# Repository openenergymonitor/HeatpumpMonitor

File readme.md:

# Heatpump Monitor

This is a technical github repository for OpenEnergyMonitor open hardware and software heat-pump performance monitoring development.

## Rationale

Heat-pumps are a key component of zero carbon energy systems making it possible to provide heating efficiently from renewable energy, they are featured in many zero carbon energy scenarios such as ZeroCarbonBritain developed by the Centre for Alternative Technology and are also highlighted in David MacKay's book Sustainable Energy without the hot air.

By monitoring a heat-pump its possible to see how well it is working, diagnose problems and get a better understanding of how a key potentially zero carbon heating solution works, data gathered and shared from well performing systems could help de-mystify heat-pump operation and help improve performance by diagnosing any problems early.

## Getting started

The heat pump monitoring application guide in the main OpenEnergyMonitor guide is a good place to start, covering the different options, including the use of the main OpenEnergyMonitor hardware:

[https://guide.openenergymonitor.org/applications/heatpump](https://guide.openenergymonitor.org/applications/heatpump)

## Hardware

### EmonPi or EmonTx based heat pump monitor

<table>
<tr><td>

</td><td>
<b>Electricity consumption and system temperatures</b><br>
<p>Monitor electricity consumption and system temperatures using clip-on CT sensors and one-wire temperature sensors connected to an emonPi or emonTx. This provides the simplest solution for installation on existing systems. See <a href="https://guide.openenergymonitor.org/applications/heatpump">main guide for details</a>.</p>
</td>
</tr>
<tr><td>

</td><td>
<b>Using external MBUS reader module</b><br>
<p>An external MBUS reader connected to the emonPi or emonBase can be used to read from high accuracy electricity and heat meters. See <a href="https://guide.openenergymonitor.org/applications/heatpump">main guide for details</a>.</p>
</td>
</tr>
</table>

### [New: RaspberryPi & MBUS based heat pump monitor](HeatpumpMonitorPi)

<table>
<tr><td>

</td><td>
<p>This is a new heat pump monitor board designed specifically for interfacing with MID standard electricity and heat meters via MBUS. It has a RaspberryPi at it’s core running our emonSD image enabling local or/and remote logging and data visualisation.</p>
</td>
</tr>
</table>

### [Original through-hole heat pump monitor](HeatpumpMonitorTH)

<table>
<tr><td>

</td><td>
<b>Main Features:</b><br>
<ul>
<li>CT current and ACAC voltage based electricity monitoring</li>
<li>Pulse counting or IRDA Elster meter reader</li>
<li>Analog inputs for Vortex Flow Sensor (VFS) option (e.g Sika, Grundfos)</li>
<li>MBUS reader for kamstrup heat meters (402, 403)</li>
<li>4x individually broken out DS18B20 temperature sensor connections</li>
<li>Arduino ATmega328 core</li>
<li>Connectivity options: ESP-12 WIFI, RaspberryPI header, RFM69</li>
</ul>
</td>
</tr>
</table>

### Mini Boards

**USB to MBUS**

- [USB to MBUS v1 SMT](https://github.com/openenergymonitor/HeatpumpMonitor/tree/master/USB_MBUS_Reader)

**WiFi MBUS Reader**

- [WiFi MBUS Reader v1 (Through-hole)](https://github.com/openenergymonitor/HeatpumpMonitor/tree/master/Hardware/WiFi_MBUS_Reader/v1_TH)
- [WiFi MBUS Reader v1 SMT](https://github.com/openenergymonitor/HeatpumpMonitor/tree/master/Hardware/WiFi_MBUS_Reader/v1)

## Heat pump monitoring dashboard

Emoncms includes an application specific heat pump dashboard available in the Apps module. The following video gives a good overview of what this dashboard can do, how to access daily electricity consumption and heat output data as well as detailed system temperature and power data.

There's also a little feature shown briefly at the end that simulates the heat output and COP of the heat pump based on the Carnot COP equation.

[YouTube: Introduction to the Emoncms heat pump dashboard](https://www.youtube.com/watch?v=jBY1Sx3LR2o)

It's also worth checking out David Bowen (@MyForest on the forum's) heat pump app, see forum post: [Heat Pump Experimentation App - Release News](https://community.openenergymonitor.org/t/heat-pump-experimentation-app-release-news/13423).

The My Heatpump app includes a feature to simulate the COP and heat output of a heat pump from the flow temperature, outside temperature and electrical power input. The equations used are documented here: https://github.com/emoncms/dynamic/blob/master/docs/heatpumpmodel.md

## Blogs and further reading

- **Blog post:** [Heatpumps in the ZeroCarbonBritain model by the Centre for Alternative Technology.](https://blog.openenergymonitor.org/2015/12/heatpumps-in-zerocarbonbritain-model-by)
- **Blog post:** [Heat pump Testing: Initial results](https://blog.openenergymonitor.org/2016/02/heat-pump-testing-initial-results)
- **[John Cantor's heat pump monitoring blog](https://heatpumps.co.uk/technical/energy-monitoring)**

## Licence

This project is open source software and hardware.

The Arduino firmware is available under the GPL v3 Licence. 

The Web Dashboard is available under the GNU Affero General Public License and is based on emoncms.

The hardware design (schematics, board files and gerber) files are licensed under the [Creative Commons Attribution-ShareAlike 3.0 Unported License](http://creativecommons.org/licenses/by-sa/3.0/) and follow the terms of the [OSHW (Open-source hardware) Statement of Principles 1.0.](http://freedomdefined.org/OSHW)

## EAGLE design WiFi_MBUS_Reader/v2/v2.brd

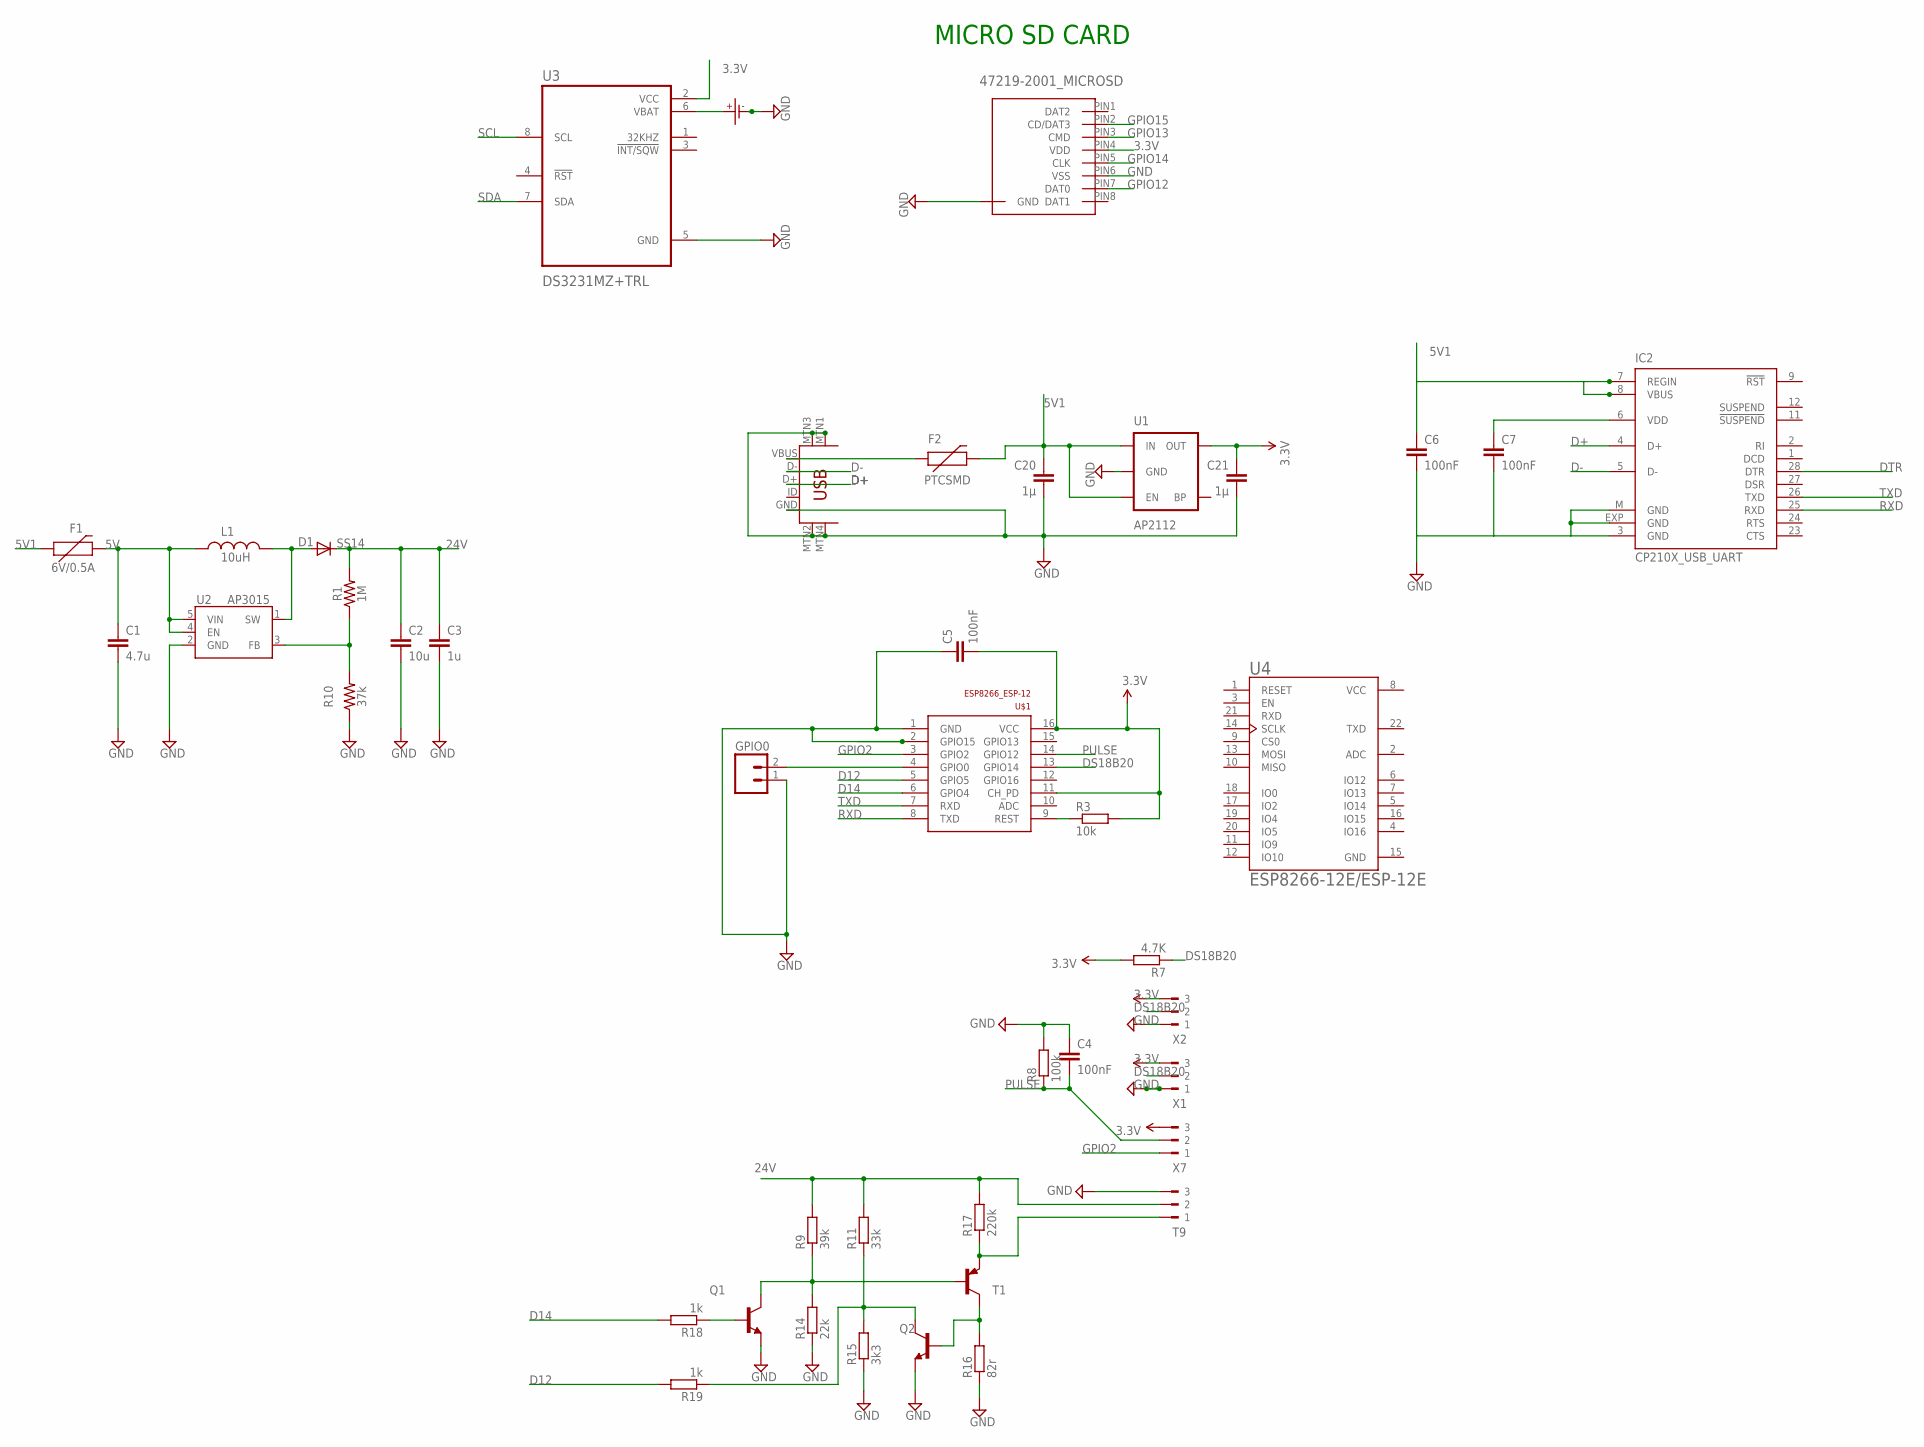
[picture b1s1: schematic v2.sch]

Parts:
C1: 4.7u; 0805
C2: 10u; 1206
C3: 1u; 1206
C4, C5: 100nF; C0603
C6, C7: 100nF; 0603-CAP
C20, C21: 1µ; C0603
CR1: CR1220SMD; MPN Harwin S8411-45R
D1: SS14; SOD-123
F1: 6V/0.5A; 1206
F2: PTCSMD; PTC-1206
GPIO0: M02PTH; 1X02
IC2: CP210X_USB_UART; MLP28
L1: 10uH; CR54
MICRO_SD: 47219-2001_MICROSD
Q1, Q2: BC808-NPN-SOT23-BEC; SOT23-BEC
R1: 1M; 0805
R3: 10k; R0603
R7: 4.7K; R0603
R8: 100k; R0603
R9: 39k; R0603
R10: 37k; 0805
R11: 33k; R0603
R14: 22k; R0603
R15: 3k3; R0603
R16: 82r; R0603
R17: 220k; R0603
R18, R19: 1k; R0603
T1: BC807-16-PNP-SOT23-BEC; SOT23-BEC
T9: 180-3
U1: AP2112; SOT23-5
U2: AP3015; SOT-23-5
U3: DS3231MZ+TRL; SOIC127P600X175-8N
U4: ESP8266-12E/ESP-12E; XCVR_ESP8266-12E/ESP-12E
U$1: ESP8266_ESP-12; ESP8266-ESP12
U$10: USB-MINIB-5PIN; USB-MINIB-CISECO
X1, X2, X7: 180-3

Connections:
3.3V: C5.2, C21.1, MICRO_SD.PIN4 (VDD), R3.2, R7.2, U1.5 (OUT), U3.2 (VCC), U$1.11 (CH_PD), U$1.16 (VCC), X1.3, X2.3, X7.3
5V: C1.1, F1.2, L1.P$1 (1), U2.4 (EN), U2.5 (VIN)
5V1: C6.1, C20.1, F1.1, F2.2, IC2.7 (REGIN), IC2.8 (VBUS), U1.1 (IN), U1.3 (EN)
24V: C2.1, C3.1, D1.C, R1.2, R9.2, R11.2, R17.2, T9.2
D12: R19.2, U$1.5 (GPIO5)
D14: R18.2, U$1.6 (GPIO4)
D+: IC2.4 (D+), U$10.D+
D-: IC2.5 (D-), U$10.D-
DS18B20: R7.1, U$1.13 (GPIO14), X1.2, X2.2
DTR: IC2.28 (DTR)
GND: C1.2, C2.2, C3.2, C4.1, C5.1, C6.2, C7.2, C20.2, C21.2, CR1.P- (P$-), GPIO0.1, IC2.3 (GND), IC2.EXP (GND), IC2.M (GND), MICRO_SD.P$1 (GND), MICRO_SD.P$2 (GND), MICRO_SD.P$3 (GND), MICRO_SD.P$4 (GND), MICRO_SD.PIN6 (VSS), Q1.E, Q2.E, R8.2, R10.1, R14.1, R15.1, R16.1, T9.3, U1.2 (GND), U2.2 (GND), U3.5 (GND), U4.15 (GND), U$1.1 (GND), U$1.2 (GPIO15), U$10.GND, U$10.MTN1 (MTN2), U$10.MTN2 (MTN3), U$10.MTN3 (MTN1), U$10.MTN4, X1.1, X2.1
GPIO2: U$1.3 (GPIO2), X7.1
GPIO12: MICRO_SD.PIN7 (DAT0)
GPIO13: MICRO_SD.PIN3 (CMD)
GPIO14: MICRO_SD.PIN5 (CLK)
GPIO15: MICRO_SD.PIN2 (CD/DAT3)
unnamed: C7.1, IC2.6 (VDD)
unnamed: F2.1, U$10.VBUS
unnamed: R1.1, R10.2, U2.3 (FB)
unnamed: D1.A, L1.P$2 (2), U2.1 (SW)
unnamed: CR1.P+ (P$+), U3.6 (VBAT)
unnamed: R17.1, T1.E, T9.1
unnamed: Q2.B, R16.2, T1.C
unnamed: Q1.C, R9.1, R14.2, T1.B
unnamed: Q2.C, R11.1, R15.2, R19.1
unnamed: Q1.B, R18.1
unnamed: GPIO0.2, U$1.4 (GPIO0)
unnamed: R3.1, U$1.9 (REST)
PULSE: C4.2, R8.1, U$1.14 (GPIO12), X7.2
RXD: IC2.25 (RXD), U$1.8 (TXD)
SCL: U3.8 (SCL)
SDA: U3.7 (SDA)
TXD: IC2.26 (TXD), U$1.7 (RXD)
VCC: U4.8 (VCC)

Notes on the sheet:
MICRO SD CARD

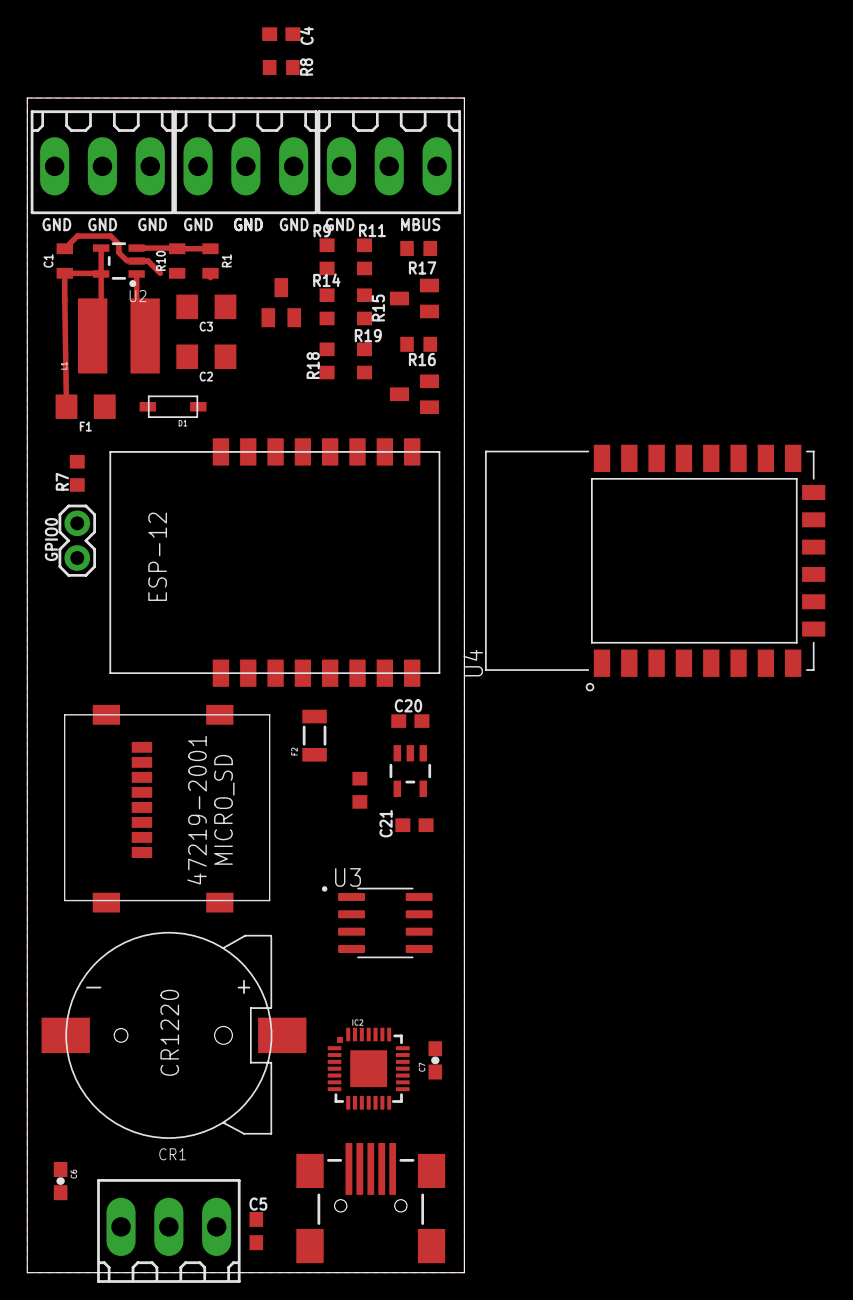
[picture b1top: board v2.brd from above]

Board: 2 copper layers, 32.0 x 86.0 mm, 44 parts (1 on the bottom side), 26 nets.

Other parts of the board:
LOGO1: OSHW_LOGO_6MILX0200-NT; OSHW_6X200_NOTEXT

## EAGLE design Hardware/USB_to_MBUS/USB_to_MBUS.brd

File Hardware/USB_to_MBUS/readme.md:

# USB to MBUS

A simple USB MBUS reader with on-board boost converter and CP2102 USB to UART chip. Designed for reading data from heat pump heat meters and interfacing directly with a RaspberryPi via a USB cable.

**Features**

- MBUS Reader circuit (original circuit by [Tomas Menzi](https://github.com/rscada/libmbus/tree/master/hardware))
- On-board boost converter (based on [Taaralabs](https://taaralabs.eu/m-bus-uart-converter/))
- CP2102 USB to UART chip

**Software**

The board can be used with the EmonHub MBUS Interfacer. This interfacer is designed to look for specific useful parameters for electric and heat metering (It does not implement the full MBUS spec). It will typically return flow and return temperatures, flow rate, heat output, and cumulative heat energy for heat meters that support these parameters.

https://guide.openenergymonitor.org/integrations/emonhub-interfacers/#mbus-reader-for-electric-and-heat-meters

## Schematic

[USB_to_MBUS.sch](USB_to_MBUS.sch)

## Board

[USB_to_MBUS.brd](USB_to_MBUS.brd)

The hardware design (schematics, board files and gerber) files are licensed under the [Creative Commons Attribution-ShareAlike 3.0 Unported License](http://creativecommons.org/licenses/by-sa/3.0/) and follow the terms of the [OSHW (Open-source hardware) Statement of Principles 1.0.](http://freedomdefined.org/OSHW)

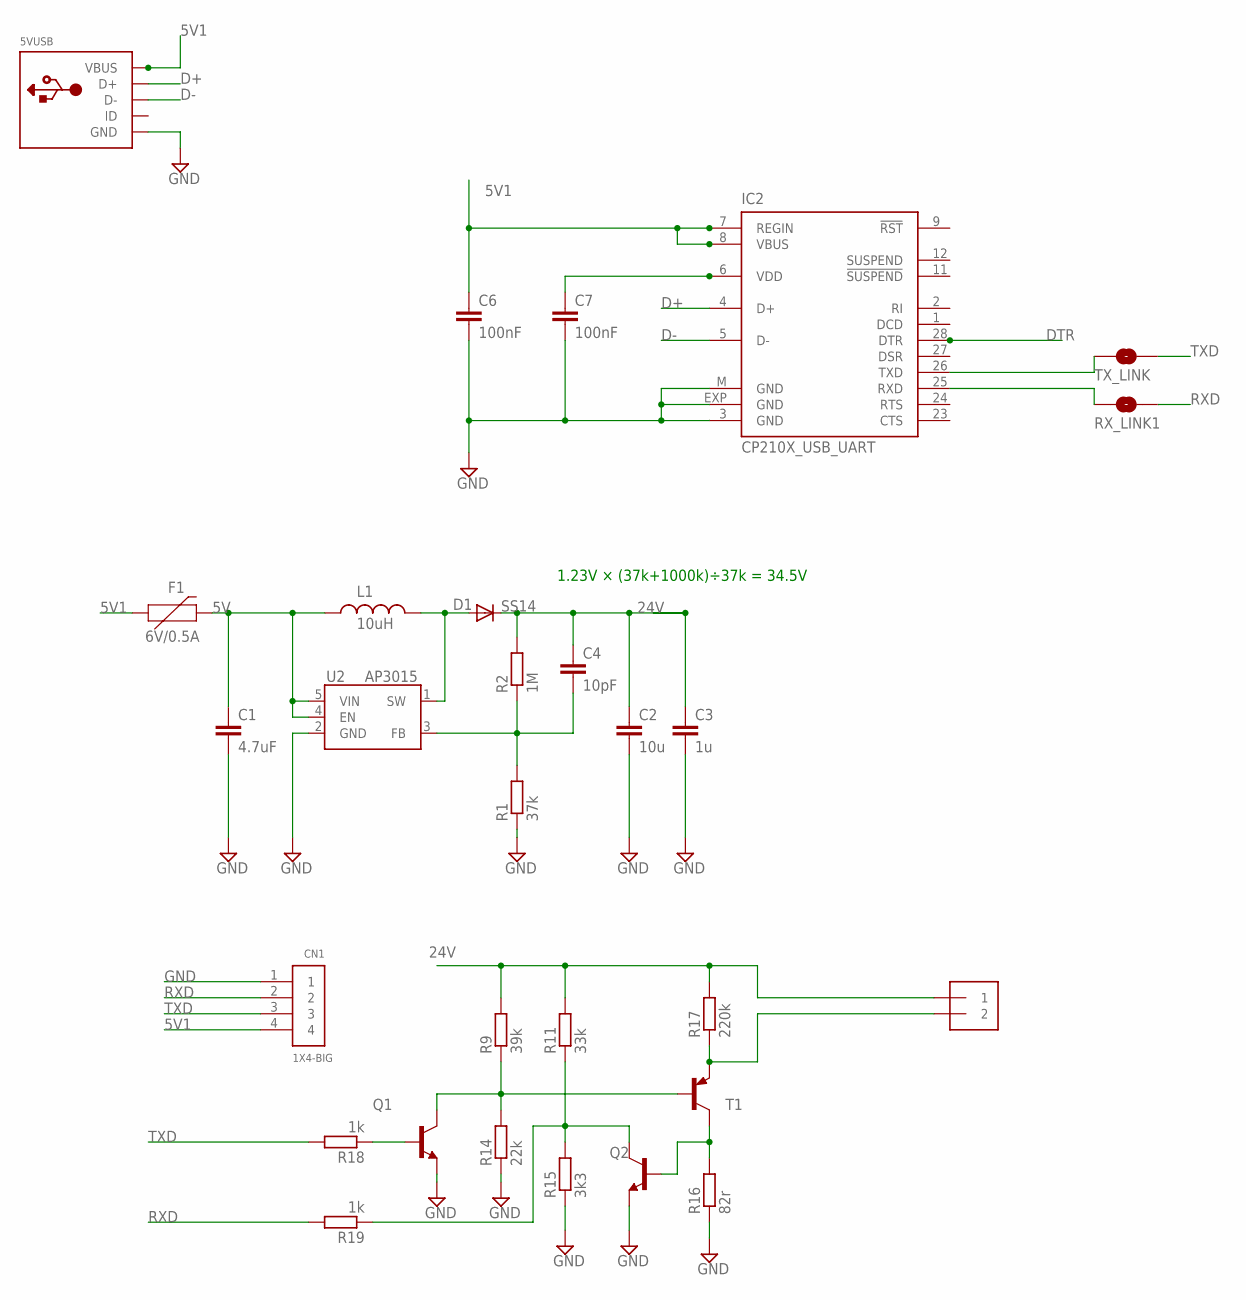
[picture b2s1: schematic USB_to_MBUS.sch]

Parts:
5VUSB: USBMOLEX; USB-MINIB-THM-MOLEX
C1: 4.7uF; 0603
C2: 10u; 1206
C3: 1u; 1206
C4: 10pF; 0603-CAP
C6, C7: 100nF; 0603-CAP
CN1: 1X4-BIG; 1X04-BIG
D1: SS14; SOD-123
F1: 6V/0.5A; 1206
IC2: CP210X_USB_UART; MLP28
J1: 1X2-3.5MM
L1: 10uH; CR54
Q1, Q2: BC808-NPN-SOT23-BEC; SOT23-BEC
R1: 37k; R0603
R2: 1M; R0603
R9: 39k; R0603
R11: 33k; R0603
R14: 22k; R0603
R15: 3k3; R0603
R16: 82r; R0603
R17: 220k; R0603
R18, R19: 1k; R0603
RX_LINK1: SOLDERJUMPERNC; SJ_2S
T1: BC807-16-PNP-SOT23-BEC; SOT23-BEC
TX_LINK: SOLDERJUMPERNC; SJ_2S
U2: AP3015; SOT-23-5

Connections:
5V: C1.1, F1.2, L1.P$1 (1), U2.4 (EN), U2.5 (VIN)
5V1: 5VUSB.VBUS, C6.1, CN1.4, F1.1, IC2.7 (REGIN), IC2.8 (VBUS)
24V: C2.1, C3.1, C4.1, D1.C, J1.1, R2.2, R9.2, R11.2, R17.2; also elsewhere on the board
D+: 5VUSB.D+, IC2.4 (D+)
D-: 5VUSB.D-, IC2.5 (D-)
DTR: IC2.28 (DTR)
GND: 5VUSB.GND, C1.2, C2.2, C3.2, C6.2, C7.2, CN1.1, IC2.3 (GND), IC2.EXP (GND), IC2.M (GND), Q1.E, Q2.E, R1.1, R14.1, R15.1, R16.1, U2.2 (GND)
unnamed: C7.1, IC2.6 (VDD)
unnamed: C4.2, R1.2, R2.1, U2.3 (FB)
unnamed: D1.A, L1.P$2 (2), U2.1 (SW)
unnamed: IC2.26 (TXD), TX_LINK.1
unnamed: IC2.25 (RXD), RX_LINK1.1
unnamed 12: J1.2, R17.1, T1.E; also elsewhere on the board
unnamed: Q2.B, R16.2, T1.C
unnamed: Q1.C, R9.1, R14.2, T1.B
unnamed: Q2.C, R11.1, R15.2, R19.1
unnamed: Q1.B, R18.1
RXD: CN1.2, R19.2, RX_LINK1.2
TXD: CN1.3, R18.2, TX_LINK.2

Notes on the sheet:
1.23V × (37k+1000k)÷37k = 34.5V

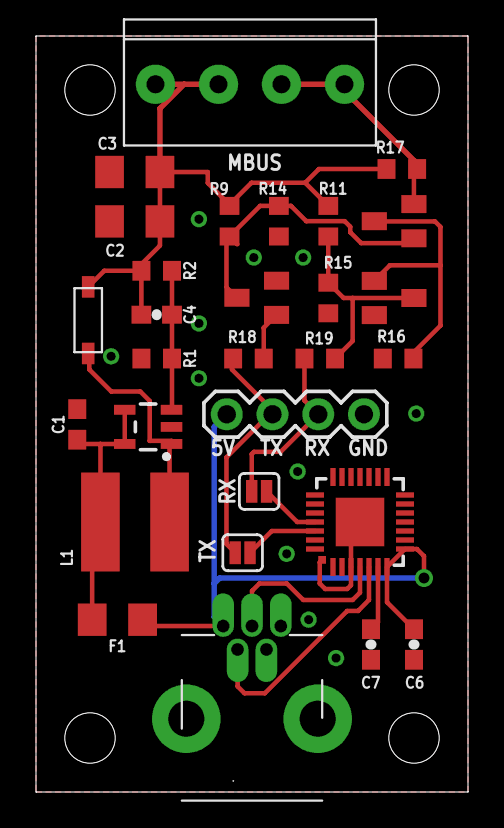
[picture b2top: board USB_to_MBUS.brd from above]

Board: 2 copper layers, 24.0 x 42.0 mm, 30 parts (1 on the bottom side), 18 nets.

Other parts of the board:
CN2: 1X4-3.5MM; 1X04-3.5MM
LOGO1: OSHW_LOGO_6MILX0200-NT; OSHW_6X200_NOTEXT

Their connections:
24V: CN2.3, CN2.4; also elsewhere on the board
unnamed 12: CN2.1, CN2.2; also elsewhere on the board

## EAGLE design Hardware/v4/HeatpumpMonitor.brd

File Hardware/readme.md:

# Heatpump monitor

This is a new design for a dedicated open source heatpump monitoring board with support for the reading of a kamstrup heatmeter or/and grundfos vortex flow sensor on board in addition to DS18B20 based temperature sensing and standard OpenEnergyMonitor electrictiy monitoring with CT current + ACAC voltage sensing.

In addition this board supports the esp-12 wifi module, raspberrypi gpio and a emonglcd display as optional extras.

This board is currently going through initial testing, if your interested in this unit and heatpump monitoring please get in contact: trystan.lea@openenergymonitor.org

## Schematic

[HeatpumpMonitor.brd](HeatpumpMonitor.brd)

## Board

[HeatpumpMonitor.sch](HeatpumpMonitor.sch)

The hardware design (schematics, board files and gerber) files are licensed under the [Creative Commons Attribution-ShareAlike 3.0 Unported License](http://creativecommons.org/licenses/by-sa/3.0/) and follow the terms of the [OSHW (Open-source hardware) Statement of Principles 1.0.](http://freedomdefined.org/OSHW)

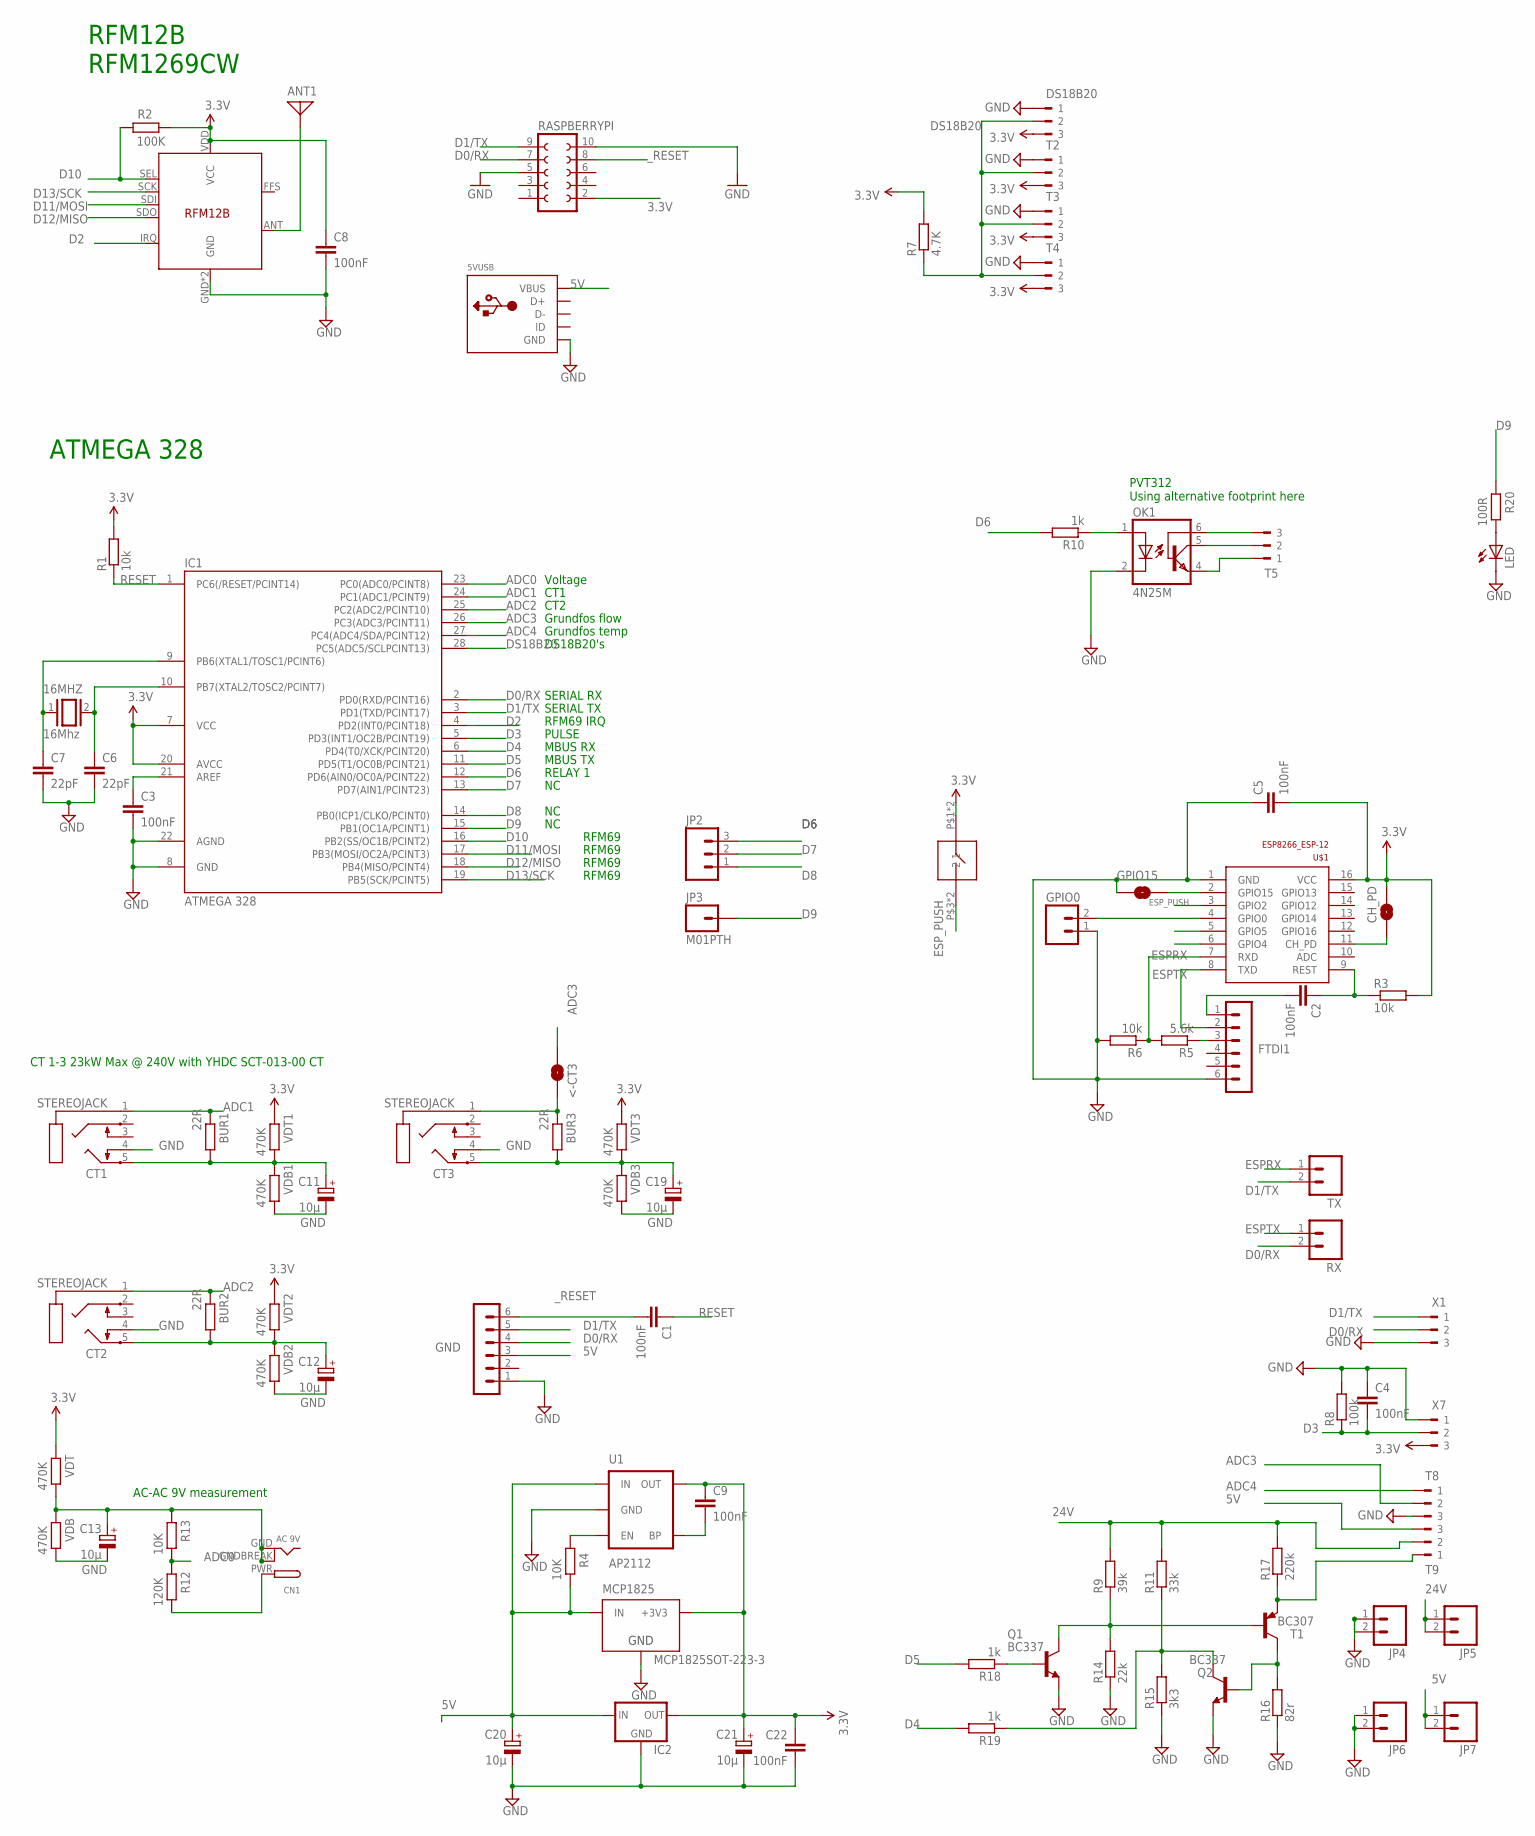
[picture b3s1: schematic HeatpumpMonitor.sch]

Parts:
5VUSB: USBMOLEX; USB-MINIB-THM-MOLEX
16MHZ: 16Mhz; QS
<-CT3: SOLDERJUMPERNO; SJ_2S-NO
ANT1: ANTENNA; PAD-01
BUR1, BUR2, BUR3: 22R; 0204/7
C1, C2, C3, C4, C5, C8, C22: 100nF; C025-024X044
C6, C7: 22pF; C2.5-2
C9: 100nF; C0603
C11, C12, C13, C19, C20, C21: 10µ; E1,8-4
CH_PD: SOLDERJUMPERNO; SJ_2S-NO
CN1: AC 9V; DCJACK_2MM_PTH
CT1, CT2, CT3: STEREOJACK; STX3100
DS18B20: 180-3
FTDI1: FTDI; MA06-1
GND: FTDI; MA06-1
GPIO0: M02PTH; 1X02
GPIO15: SOLDERJUMPERNO; SJ_2S-NO
IC1: ATMEGA 328; DIL28-3
IC2: 78XXS
JP2: M03PTH; 1X03
JP3: M01PTH; 1X01
JP4, JP5, JP6, JP7: M02PTH; 1X02
LED: LED3MM
MCP1825: MCP1825SOT-223-3; SOT-223
OK1: 4N25M; DIL06
Q1, Q2: BC337; TO92
R1, R3, R6: 10k; 0204/7
R2: 100K; 0204/7
R4: 10K; R0603
R5: 5.6k; 0204/7
R7: 4.7K; 0204/7
R8: 100k; 0207/2V
R9: 39k; 0204/7
R10, R18, R19: 1k; 0204/7
R11: 33k; 0204/7
R12: 120K; 0204/7
R13: 10K; 0204/7
R14: 22k; 0204/7
R15: 3k3; 0204/7
R16: 82r; 0204/7
R17: 220k; 0204/7
R20: 100R; 0204/7
RASPBERRYPI: FE05-2
RX: M02PTH; 1X02
T1: BC307; TO92
T2, T3, T4, T5, T8, T9: 180-3
TX: M02PTH; 1X02
U1: AP2112; SOT23-5
U$1: ESP8266_ESP-12; ESP8266-ESP12
U$2: KSEK43G"; KSEK43G
U$14: RFM12B
VDB, VDB1, VDB2, VDB3: 470K; 0204/7
VDT, VDT1, VDT2, VDT3: 470K; 0204/7
X1, X7: 180-3

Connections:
3.3V: C5.2, C8.1, C9.1, C21.+, C22.1, CH_PD.1, DS18B20.3, IC1.7 (VCC), IC1.20 (AVCC), IC2.OUT, MCP1825.3 (+3V3), R1.2, R2.1, R3.2, R7.2, RASPBERRYPI.2, T2.3, T3.3, T4.3, U1.5 (OUT), U$1.16 (VCC), U$2.P$1 (1), U$2.P$2 (1), U$14.VDD (VCC), VDT.2, VDT1.2, VDT2.2, VDT3.2, X7.3
5V: 5VUSB.VBUS, C20.+, GND.3, IC2.IN, JP7.1, JP7.2, MCP1825.1 (IN), R4.1, T9.3, U1.1 (IN)
24V: JP5.1, JP5.2, R9.2, R11.2, R17.2, T9.2
AC: CN1.PWR, R12.1
ADC0: IC1.23 (PC0(ADC0/PCINT8)), R12.2, R13.1
ADC1: BUR1.2, CT1.1, IC1.24 (PC1(ADC1/PCINT9))
ADC2: BUR2.2, CT2.1, IC1.25 (PC2(ADC2/PCINT10))
ADC3: <-CT3.2, IC1.26 (PC3(ADC3/PCINT11)), T8.2
ADC4: IC1.27 (PC4(ADC4/SDA/PCINT12)), T8.1
D0/RX: GND.4, IC1.2 (PD0(RXD/PCINT16)), RASPBERRYPI.7, RX.2, X1.2
D1/TX: GND.5, IC1.3 (PD1(TXD/PCINT17)), RASPBERRYPI.9, TX.2, X1.1
D2: IC1.4 (PD2(INT0/PCINT18)), U$14.IRQ
D3: C4.2, IC1.5 (PD3(INT1/OC2B/PCINT19)), R8.1, X7.2
D4: IC1.6 (PD4(T0/XCK/PCINT20)), R19.2
D5: IC1.11 (PD5(T1/OC0B/PCINT21)), R18.2
D6: IC1.12 (PD6(AIN0/OC0A/PCINT22)), JP2.3, R10.2
D7: IC1.13 (PD7(AIN1/PCINT23)), JP2.2
D8: IC1.14 (PB0(ICP1/CLKO/PCINT0)), JP2.1
D9: IC1.15 (PB1(OC1A/PCINT1)), JP3.1, R20.2
D10: IC1.16 (PB2(SS/OC1B/PCINT2)), R2.2, U$14.SEL
D11/MOSI: IC1.17 (PB3(MOSI/OC2A/PCINT3)), U$14.SDI
D12/MISO: IC1.18 (PB4(MISO/PCINT4)), U$14.SDO
D13/SCK: IC1.19 (PB5(SCK/PCINT5)), U$14.SCK
DIG1: ANT1.1, U$14.ANT
DS18B20: DS18B20.2, IC1.28 (PC5(ADC5/SCLPCINT13)), R7.1, T2.2, T3.2, T4.2
ESPRX: R5.2, R6.1, TX.1, U$1.7 (RXD)
ESPTX: FTDI1.2, RX.1, U$1.8 (TXD)
ESP_PUSH: U$1.3 (GPIO2), U$2.P$3 (2), U$2.P$4 (2)
GND: 5VUSB.GND, C3.2, C4.1, C5.1, C6.2, C7.2, C8.2, C11.-, C12.-, C13.-, C19.-, C20.-, C21.-, C22.2, CT1.4, CT2.4, CT3.4, DS18B20.1, FTDI1.6, GND.1, GPIO0.1, GPIO15.2, IC1.8 (GND), IC1.22 (AGND), IC2.GND, JP4.1, JP4.2, JP6.1, JP6.2, LED.K (C), MCP1825.2 (GND), OK1.2 (C), Q1.1 (E), Q2.1 (E), R6.2, R8.2, R14.1, R15.1, R16.1, RASPBERRYPI.5, RASPBERRYPI.10, T2.1, T3.1, T4.1, T8.3, U1.2 (GND), U$1.1 (GND), U$14.GND, U$14.P$12 (GND), VDB.1, VDB1.1, VDB2.1, VDB3.1, X1.3, X7.1
unnamed: 16MHZ.2, C6.1, IC1.10 (PB7(XTAL2/TOSC2/PCINT7))
unnamed: BUR2.1, C12.+, CT2.5, VDB2.2, VDT2.1
unnamed: C2.2, FTDI1.1
unnamed: <-CT3.1, BUR3.2, CT3.1
unnamed: OK1.1 (A), R10.1
unnamed: OK1.6 (BAS), T5.3
unnamed: C9.2, U1.4 (BP)
unnamed: BUR3.1, C19.+, CT3.5, VDB3.2, VDT3.1
unnamed: OK1.5 (COL), T5.2
unnamed: OK1.4 (EMI), T5.1
unnamed: R4.2, U1.3 (EN)
unnamed: 16MHZ.1, C7.1, IC1.9 (PB6(XTAL1/TOSC1/PCINT6))
unnamed: R17.1, T1.1 (E), T9.1
unnamed: LED.A, R20.1
unnamed: Q2.2 (B), R16.2, T1.3 (C)
unnamed: Q1.3 (C), R9.1, R14.2, T1.2 (B)
unnamed: C3.1, IC1.21 (AREF)
unnamed: Q2.3 (C), R11.1, R15.2, R19.1
unnamed: Q1.2 (B), R18.1
unnamed: GPIO15.1, U$1.2 (GPIO15)
unnamed: GPIO0.2, U$1.4 (GPIO0)
unnamed: C13.+, CN1.GND, CN1.GNDBREAK, R13.2, VDB.2, VDT.1
unnamed: FTDI1.3, R5.1
unnamed: BUR1.1, C11.+, CT1.5, VDB1.2, VDT1.1
unnamed: CH_PD.2, U$1.11 (CH_PD)
unnamed: C2.1, R3.1, U$1.9 (REST)
RESET: C1.1, IC1.1 (PC6(/RESET/PCINT14)), R1.1
_RESET: C1.2, GND.6, RASPBERRYPI.8

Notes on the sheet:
ATMEGA 328
RFM12B RFM1269CW
CT 1-3 23kW Max @ 240V with YHDC SCT-013-00 CT
AC-AC 9V measurement
Voltage
CT1
CT2
SERIAL RX
SERIAL TX
RFM69 IRQ
MBUS RX
MBUS TX
PULSE
Grundfos flow
Grundfos temp
DS18B20's
RELAY 1
RFM69
PVT312 Using alternative footprint here

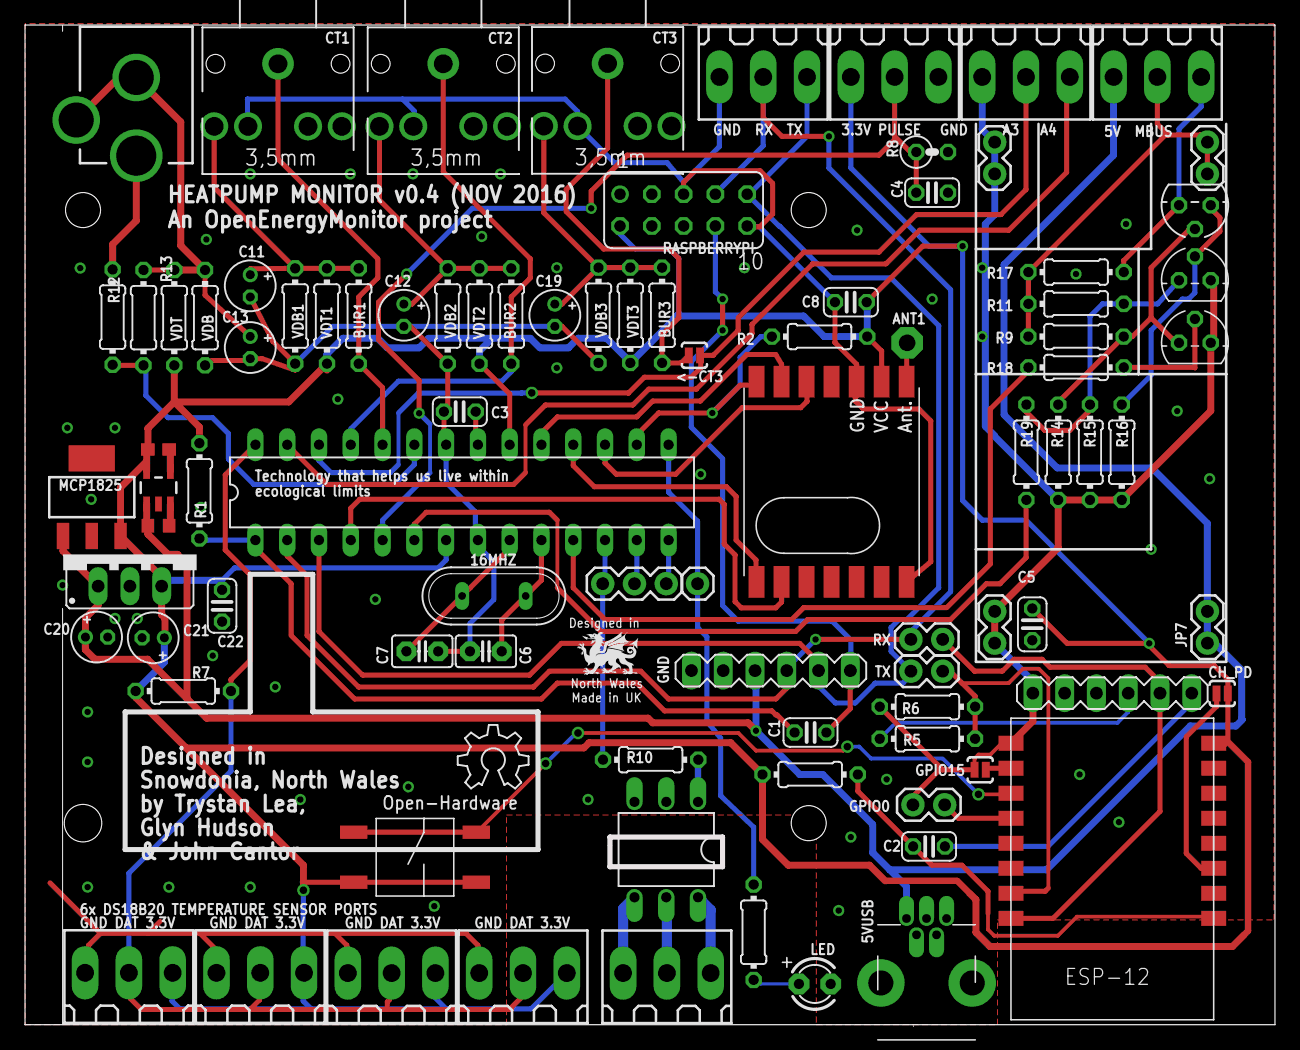
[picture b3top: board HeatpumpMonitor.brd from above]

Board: 2 copper layers, 99.9 x 79.9 mm, 91 parts (0 on the bottom side), 57 nets.

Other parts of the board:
LOGO1: OSHW_LOGO_6MILX0200-NT; OSHW_6X200_NOTEXT

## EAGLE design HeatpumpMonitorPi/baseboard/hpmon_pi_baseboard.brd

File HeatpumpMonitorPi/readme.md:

## RaspberryPi, MBUS & Modbus based heat pump monitor

This is a new heat pump monitor board designed specifically for interfacing with MID standard electricity and heat meters via MBUS or/and Modbus. It has a RaspberryPi at it’s core running our emonSD image enabling local or/and remote logging and data visualisation.

It is designed for monitoring heat pump electricity consumption, heat output and system temperatures for detailed performance analysis & troubleshooting.

### Features

- MBUS Reader (Reads from heat meters and some electric meters, though the SDM120-MBUS is no longer recommended)
- A Modbus Reader is recommended for reading from SDM120-Modbus electricity meters
- DS18B20 Temperature sensor connections
- 6 Digital input or outputs can be used for pulse counting
- I2C connection (uses 2 of the 6 digital IO's)
- RaspberryPi running the OpenEnergyMonitor emonSD image

This hardware design combines in a single unit a: 

- RaspberryPi
- [Heat pump monitoring baseboard](baseboard)
- [USB to MBUS reader](../USB_MBUS_Reader)

### Selecting a heat meter

Please read our guide on selecting the right heat meter here:<br>https://github.com/openenergymonitor/HeatpumpMonitor/blob/master/selectingheatmeter.md

### Connection diagram

### Setup

The following setup instructions assume an assembled heat pump monitor kit as shown in the picture above, with pre-prepared SD card running the standard emonSD image inserted into the RaspberryPi **(with SSH enabled, see [Guide: Credentials](https://guide.openenergymonitor.org/technical/credentials/))**.

1. Use the connection diagram above to connect MBUS meters, temperature sensors and power. There are two A and B MBUS terminals that can be used to simplify connecting two meters to the MBUS reader. Make sure that the power supply is capable of supplying 2A e.g [OpenEnergyMonitor Shop 5V USB Power Adapter](https://shop.openenergymonitor.com/5v-dc-usb-power-adapter-uk-plug) (MBUS data corruption can occur if the power supply output is too low).

2. Power up the unit, wait a couple of minutes for the Pi to create a WiFi access point. Connect to the access point and then use the WiFi configuration interface to connect the unit to your home WiFi. See [Guide: Connect](https://guide.openenergymonitor.org/setup/connect/) for full details.

3. If you have connected DS18B20 temperature sensors a couple of minor steps are required to enable reading from DS18B20 temperature sensors on the Pi. Follow steps 1 to 4 here [EmonHub Interfacers: Direct DS18B20 temperature sensing](https://guide.openenergymonitor.org/integrations/emonhub-interfacers/#direct-ds18b20-temperature-sensing).

4. EmonHub is piece of software running on the Pi that reads from the connected MBUS meters and DS18B20 temperature sensors. It then forwards the data to a seperate piece of software called Emoncms for data storage and visualisation. EmonHub is configured using a configuration file located at: /etc/emonhub/emonhub.conf. A configuration example is included at the bottom of this page for reading from a SDM120-MBUS electricity meter, a Qalcosonic E3 heat meter and DS18B20 temperature sensors. Overwrite the existing default configuration with this configuration as it is a better starting point for our requirements.

5. Configure EmonHub MBUS settings. The default MBUS configuration settings below assumes that a suitable heat meter is connected on address 1. You may need to adjust the MBUS address of either of the meters to ensure that they are not both on the same address. See instructions in the forum post here on how to do this: https://community.openenergymonitor.org/t/reading-from-multiple-mbus-meters-with-the-emonhub-mbus-interfacer/18159

6. Example configuration with a Sontex 531 heat meter:

```
[[MBUS]]
    Type = EmonHubMBUSInterfacer
    [[[init_settings]]]
        device = /dev/ttyAMA0
        baud = 2400
    [[[runtimesettings]]]
        pubchannels = ToEmonCMS,
        read_interval = 10
        validate_checksum = False
        nodename = mbus
        [[[[meters]]]]
            [[[[[sontex]]]]]
                address = 1
                type = sontex531
```

7. With the hardware connected up and the settings in place, data should now be coming in and be listed as inputs in Emoncms.

### Using the EmonHub log to debug issues reading data from the meters

...

### Configuring Emoncms

...

### Example test setup

Reading from a SDM120-MBUS electricity meter and a Qalcosonic E3 heat meter. These, or similar meters would usually be installed as part of heat pump installation. 

**Note:** The SDM120-MBUS electricity meter is no longer recommended due to reliability issues. We now recommend to use a SDM120-Modbus meter with a seperate Modbus reader. See forum post: [https://community.openenergymonitor.org/t/sdm120-mbus-meter-freezing-drop-out/20765/2](https://community.openenergymonitor.org/t/sdm120-mbus-meter-freezing-drop-out/20765/2)

### Example EmonHub Configuration

The following is a full */etc/emonhub/emonhub.conf* example that reads from any connected DS18B20 temperature sensors, a Sontex Superstatic 440 heat meter with Multical 531 integrator on MBUS and a SDM120-Modbus electricity meter. Data is forwarded to the local emoncms installation using MQTT and the remote emoncms installation via HTTP.

```
[hub]
loglevel = DEBUG

[interfacers]

[[DS18B20]]
    Type = EmonHubDS18B20Interfacer
    [[[init_settings]]]
    [[[runtimesettings]]]
        pubchannels = ToEmonCMS,
        read_interval = 10
        nodename = temperatures

[[MBUS]]
    Type = EmonHubMBUSInterfacer
    [[[init_settings]]]
        device = /dev/ttyAMA0
        baud = 2400
    [[[runtimesettings]]]
        pubchannels = ToEmonCMS,
        read_interval = 10
        validate_checksum = False
        nodename = mbus
        [[[[meters]]]]
            [[[[[sontex]]]]]
                address = 1
                type = sontex531

[[SDM120]]
    Type = EmonHubSDM120Interfacer
    [[[init_settings]]]
        device = /dev/ttyUSB0
        baud = 2400
    [[[runtimesettings]]]
        pubchannels = ToEmonCMS,
        read_interval = 10
        nodename = SDM120

[[MQTT]]
    Type = EmonHubMqttInterfacer
    [[[init_settings]]]
        mqtt_host = 127.0.0.1
        mqtt_port = 1883
        mqtt_user = emonpi
        mqtt_passwd = emonpimqtt2016

    [[[runtimesettings]]]
        pubchannels = ToRFM12,
        subchannels = ToEmonCMS,
        nodevar_format_enable = 1
        nodevar_format_basetopic = emon/

[[emoncmsorg]]
    Type = EmonHubEmoncmsHTTPInterfacer
    [[[init_settings]]]
    [[[runtimesettings]]]
        pubchannels = ToRFM12,
        subchannels = ToEmonCMS,
        url = https://emoncms.org
        apikey = xxxxxxxxxxxxxxxxxxxxxxxxxxxxxxxx
        senddata = 1
        sendstatus = 1
        sendinterval= 30

[nodes]
```

**Forum post: Reading from multiple MBUS meters with the EmonHub MBUS interfacer**<br>
https://community.openenergymonitor.org/t/reading-from-multiple-mbus-meters-with-the-emonhub-mbus-interfacer/18159

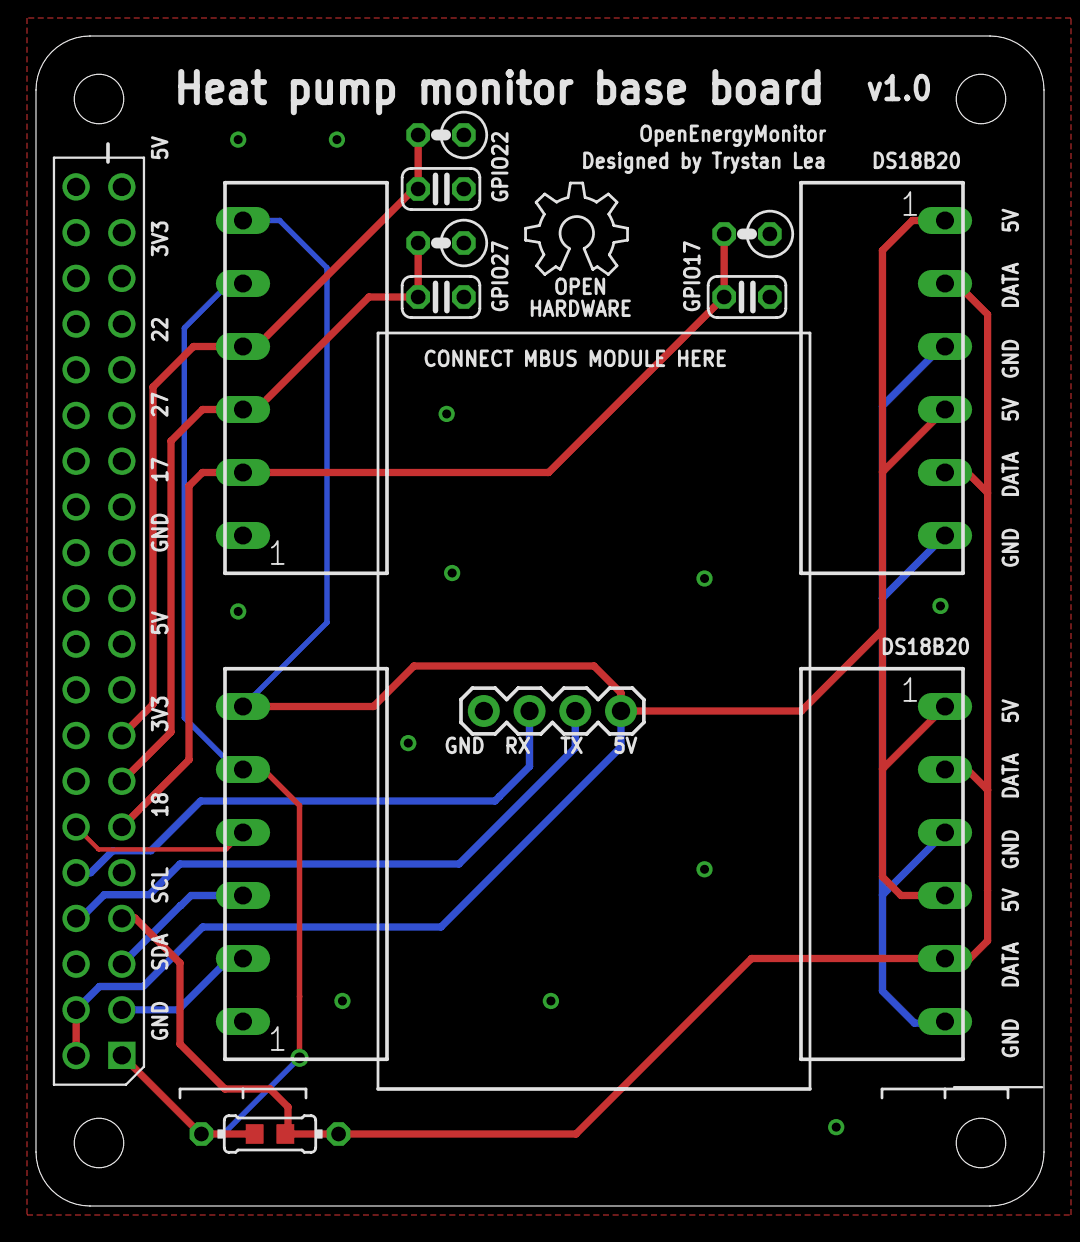
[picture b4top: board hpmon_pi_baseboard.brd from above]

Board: 2 copper layers, 56.0 x 65.0 mm, 15 parts (0 on the bottom side), 12 nets.

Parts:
C1, C2, C4: 100nF; C025-024X044
LOGO2: OSHW_LOGO_6MILX0200-NT; OSHW_6X200_NOTEXT
MBUS_SERIAL: 1X4-BIG; 1X04-BIG
PCB1: RPI3RPI3; RPI3
R1, R2, R8: 100k; 0207/2V
R7: 4.7K; 0204/7
R16: 4.7k; R0603
TB1, TB2, TB3, TB4: 3.5MM_TB_X6; 3.5MM_X6

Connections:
3V3: PCB1.P$1, R7.2, R16.2, TB1.P$5, TB2.P$5
5V: MBUS_SERIAL.1, PCB1.P$2, PCB1.P$4, TB1.P$6, TB2.P$6, TB3.P$1, TB3.P$4, TB4.P$1, TB4.P$4
DS18B20: PCB1.P$7, R7.1, R16.1, TB3.P$2, TB3.P$5, TB4.P$2, TB4.P$5
GND: C1.2, C2.2, C4.2, MBUS_SERIAL.4, PCB1.P$6, PCB1.P$9, PCB1.P$14, R1.1, R2.1, R8.1, TB1.P$1, TB2.P$1, TB3.P$3, TB3.P$6, TB4.P$3, TB4.P$6
GPIO17: C2.1, PCB1.P$11, R2.2, TB2.P$2
GPIO18: PCB1.P$12, TB1.P$4
GPIO22: C1.1, PCB1.P$15, R1.2, TB2.P$4
GPIO27: C4.1, PCB1.P$13, R8.2, TB2.P$3
RXD: MBUS_SERIAL.3, PCB1.P$10
SCL: PCB1.P$5, TB1.P$3
SDA: PCB1.P$3, TB1.P$2
TXD: MBUS_SERIAL.2, PCB1.P$8

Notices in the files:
parts and their libraries:
SparkFun-Capacitors: Licensing: Creative Commons ShareAlike 4.0 International - https://creativecommons.org/licenses/by-sa/4.0
